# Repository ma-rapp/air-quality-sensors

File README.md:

# Air Quality Sensor

This is an air quality sensor with Arduino Nano ESP32, DHT22 temperature and humidity sensor, and MH-Z19C CO₂ sensor.
See [hobby.rapp-martin.de/projects/air-quality-dashboards/](https://hobby.rapp-martin.de/projects/air-quality-dashboards/) for a description.

## Electronics

The `electronics` folder contains a KiCAD project including schematic and PCB design.

## Software

The `software` folder contains an Arduino project. Following adjustments are required:
* set WiFI SSID and password,
* set URL of the InfluxDB server, and
* set InfluxDB token.

The PCB features a DIP switch that can be used to select the sensor ID between 1 and 6.

Sensor ID 0 can be used for testing. The sensor does not push its measurements to the InfluxDB but only prints them to the serial connection.

### CO₂ calibration

Sensor ID 7 is used for CO₂ calibration. Place the sensor in the open, select sensor ID 7, and power on for CO₂ calibration. Wait until the green LED blinks. See the MH-Z19C datasheet for more details.

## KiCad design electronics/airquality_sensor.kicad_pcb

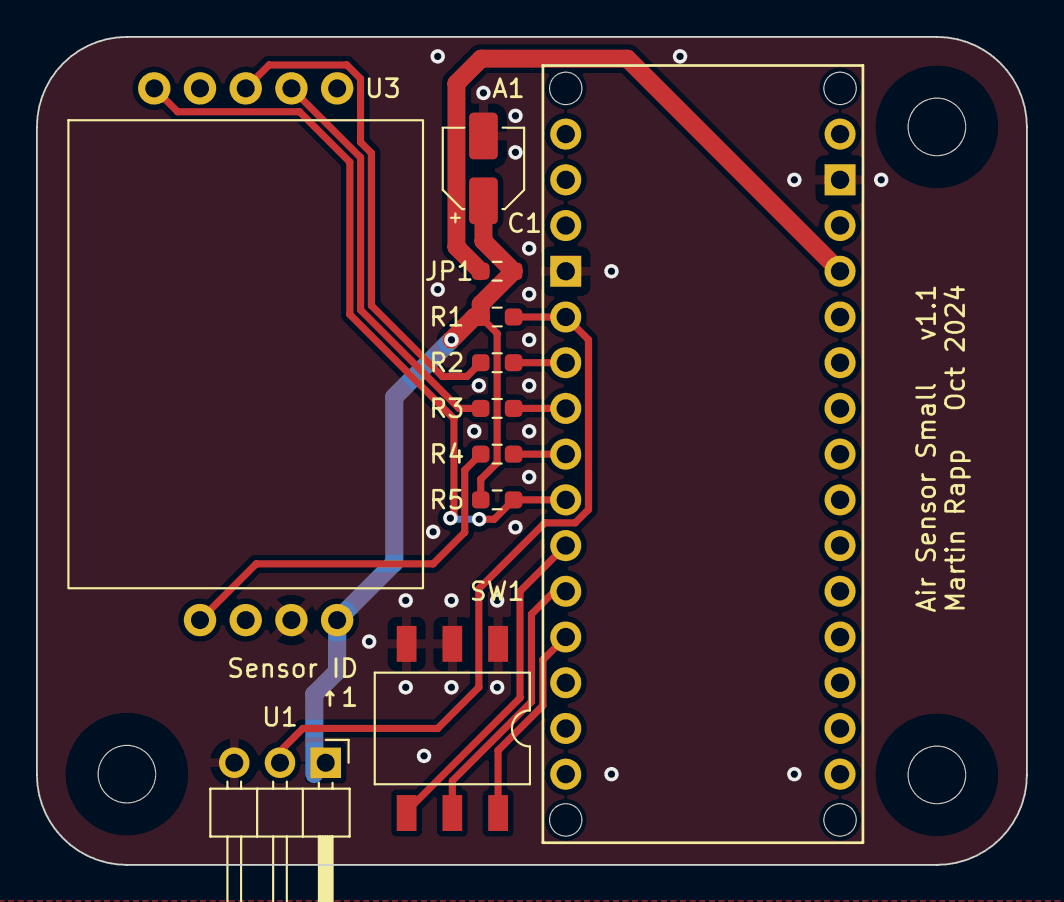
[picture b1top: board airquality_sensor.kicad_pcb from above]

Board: 2 copper layers, 55.0 x 46.0 mm, 14 parts (0 on the bottom side), 14 nets.

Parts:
A1: Arduino_Nano_ESP32_Socket
C1: 22u; CP_Elec_4x5.4
H1, H2, H3: MountingHole; MountingHole_3.2mm_M3_DIN965
JP1: Jumper_2_Bridged; R_0603_1608Metric_Pad0.98x0.95mm_HandSolder
R1, R2, R3, R4, R5: 10k; R_0603_1608Metric_Pad0.98x0.95mm_HandSolder
SW1: SW_DIP_x03; SMD_Switch-3_W7.62mm
U1: AM2302; PinHeader_1x03_P2.54mm_Horizontal_Polarized
U3: MH-Z19C-PH

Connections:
+5V: C1.1, JP1.1 (A), R1.1, R5.1, U1.1 (VDD), U3.1 (Vin)
CO2_CALIB: A1.D6, R5.2, U3.5 (Hd)
CO2_PWM: A1.D5, R4.1
CO2_RX: A1.D4, R3.1
CO2_TX: A1.D3, R2.1
GND: A1.GND1 (GND), A1.GND2 (GND), C1.2, SW1.1, SW1.2, SW1.3, U1.3 (GND), U3.2 (GND)
unnamed: A1.5V, JP1.2 (B)
unnamed: R4.2, U3.4 (PWM)
unnamed: R3.2, U3.8 (Rx)
unnamed: R2.2, U3.7 (Tx)
SENSORID1: A1.D7, SW1.4
SENSORID2: A1.D8, SW1.5
SENSORID3: A1.D9, SW1.6
TEMP_HUM: A1.D2, R1.2, U1.2 (SDA)
